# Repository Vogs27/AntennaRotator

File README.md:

# AntennaRotator
This is an improved antenna rotor based on [Satnogs Project rotor V3.1](https://wiki.satnogs.org/SatNOGS_Rotator_v3). It uses the same mechanics but a different custom made controller.

The board uses an ARM based microcontroller (SAMD21) at 48MHz, giving more headroom for future developements. It uses the Arduino Zero core to ease the programming stage. 
TMC2209 are used as drivers to provide a silent experience.

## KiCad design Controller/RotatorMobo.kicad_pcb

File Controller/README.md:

# Controller board

This is the first version of the controller board.
It's a 100mmx100mm 4 layer PCB.

An interactive bom is provided inside ibom folder.
Grbl files are in production folder together with a BOM file. Some LCSC components code are provided for reference.

The board was manufactured at JLCPCB.

## ToDo

Ground trace in TMC2209 is not connected to both ground vias but just to one. After testing this doesn't seems a problem.

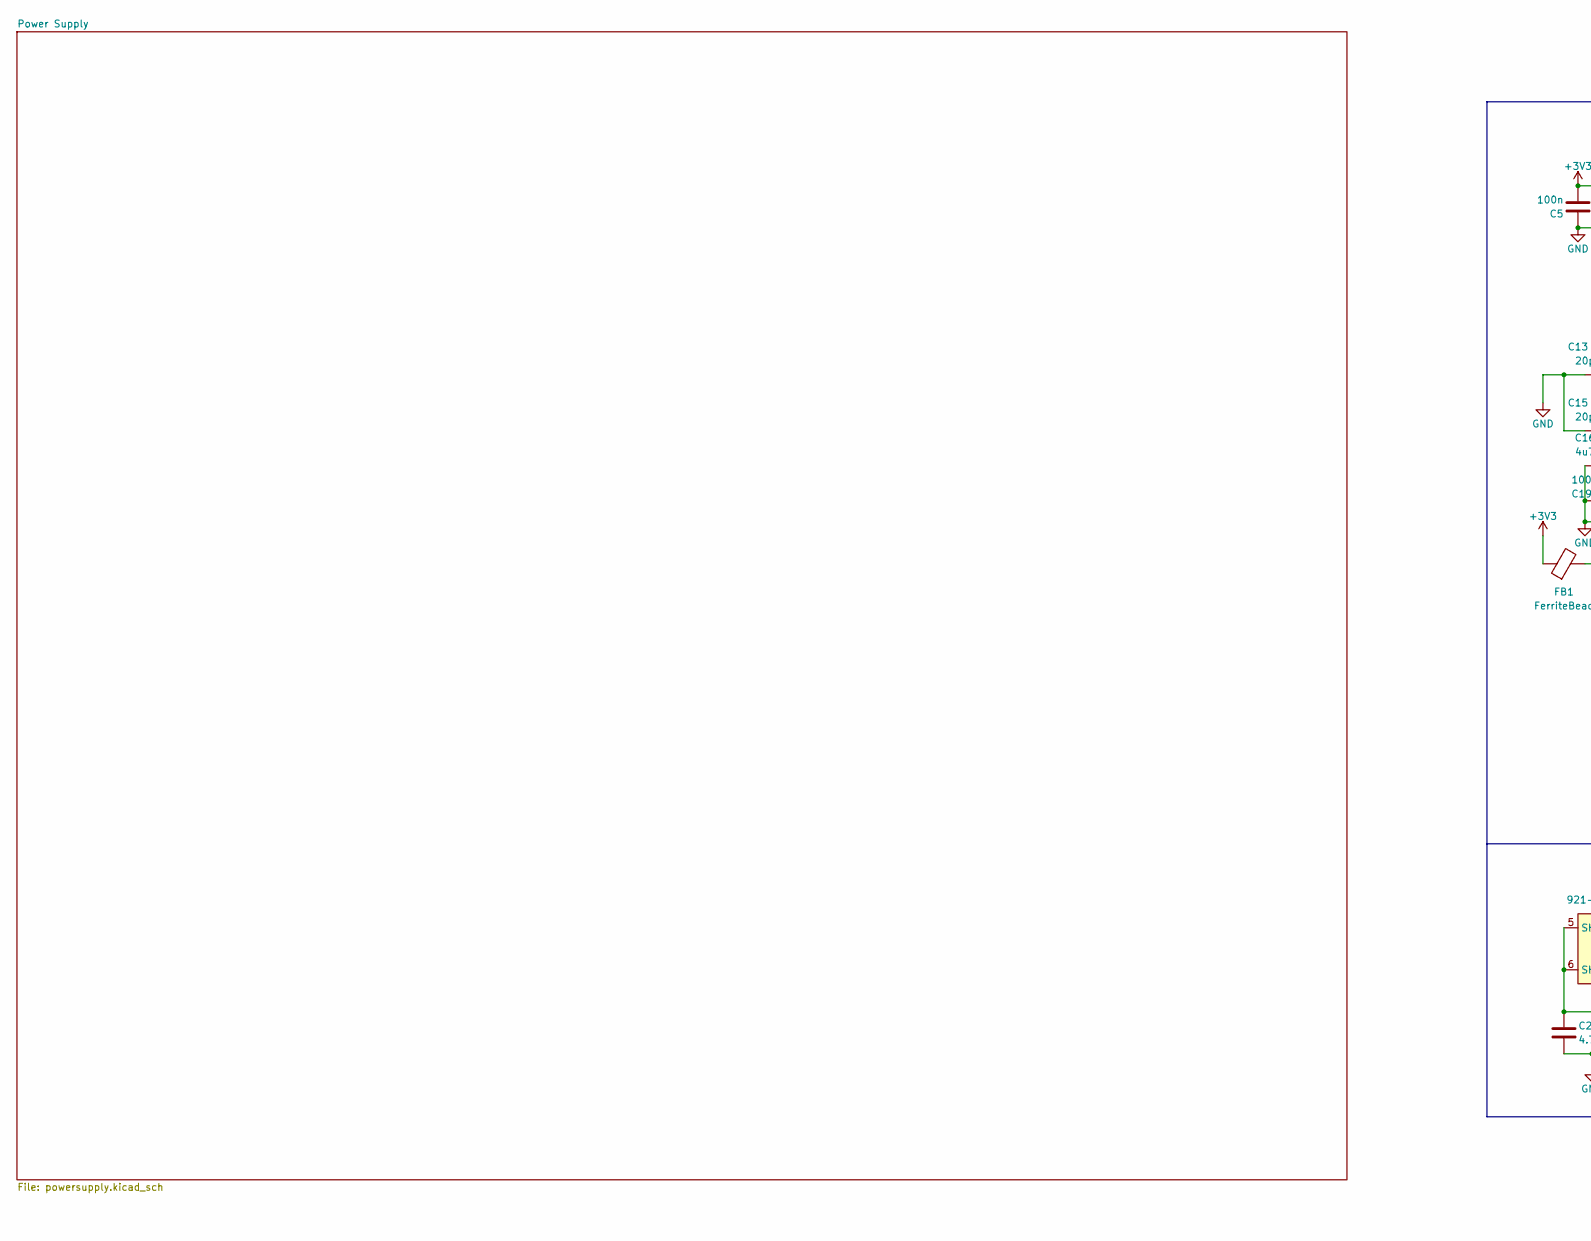
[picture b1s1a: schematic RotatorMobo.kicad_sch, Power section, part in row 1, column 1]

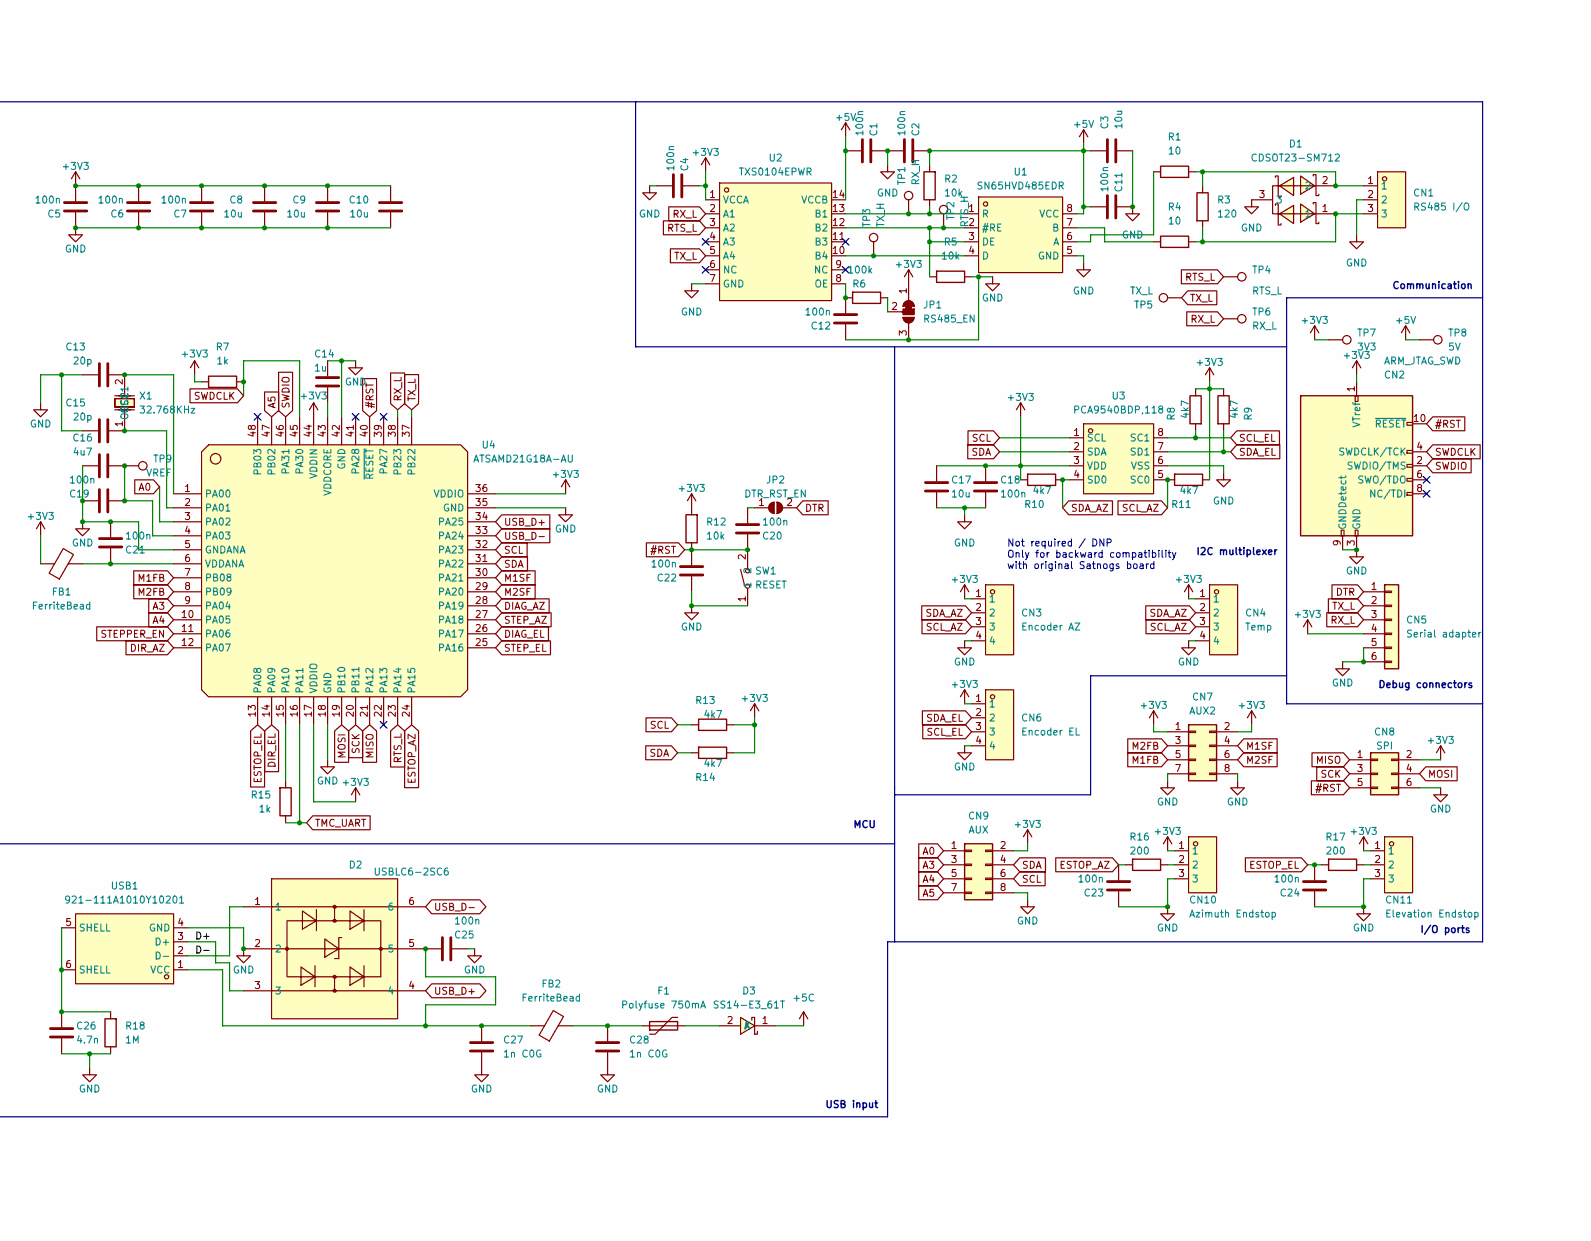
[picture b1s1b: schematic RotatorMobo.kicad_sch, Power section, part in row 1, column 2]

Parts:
C1, C2, C4, C5, C6, C7, C11, C12, C18, C19, C20, C21, C22, C23, C24, C25: 100n; C_0603_1608Metric_Pad1.08x0.95mm_HandSolder; LCSC_id C1591
C3, C8, C9, C10, C17: 10u; R_1206_3216Metric_Pad1.30x1.75mm_HandSolder; LCSC_id C89632
C13, C15: 20p; C_0805_2012Metric_Pad1.18x1.45mm_HandSolder; LCSC_id C1798
C14: 1u; C_0805_2012Metric_Pad1.18x1.45mm_HandSolder; LCSC_id C116352
C16: 4u7; C_0805_2012Metric_Pad1.18x1.45mm_HandSolder; LCSC_id C98192
C26: 4.7n; R_1206_3216Metric_Pad1.30x1.75mm_HandSolder; LCSC_id C571063
C27, C28: 1n C0G; R_0603_1608Metric_Pad0.98x0.95mm_HandSolder; LCSC_id C3909020
CN1: RS485 I/O; PinHeader_1x03_P2.54mm_Vertical; LCSC Part C5341202
CN2: ARM_JTAG_SWD; PinHeader_2x05_P1.27mm_Vertical
CN3: Encoder AZ; PinHeader_1x04_P2.54mm_Vertical; LCSC Part C722867
CN4: Temp; PinHeader_1x04_P2.54mm_Vertical; LCSC Part C722867
CN5: Serial adapter; PinHeader_1x06_P2.54mm_Vertical
CN6: Encoder EL; PinHeader_1x04_P2.54mm_Vertical; LCSC Part C722867
CN7: AUX2; PinHeader_2x04_P2.54mm_Vertical
CN8: SPI; PinHeader_2x03_P2.54mm_Vertical
CN9: AUX; PinHeader_2x04_P2.54mm_Vertical
CN10: Azimuth Endstop; PinHeader_1x03_P2.54mm_Vertical; LCSC Part C5341202
CN11: Elevation Endstop; PinHeader_1x03_P2.54mm_Vertical; LCSC Part C5341202
D1: CDSOT23-SM712; SOT-23_L2.9-W1.3-P1.90-LS2.4-BR; LCSC Part C404012
D2: USBLC6-2SC6; SOT-23-6_L2.9-W1.6-P0.95-LS2.8-BL; LCSC Part C7519
D3: SS14-E3_61T; D_SMA_Handsoldering; LCSC Part C47460
F1: Polyfuse 750mA; Fuse_0805_2012Metric_Pad1.15x1.40mm_HandSolder; LCSC_id C883111
FB1, FB2: FerriteBead; L_0603_1608Metric_Pad1.05x0.95mm_HandSolder; MPN BLM18PG471SN1; LCSC ID C97853
JP1: RS485_EN; SolderJumper-3_P1.3mm_Bridged12_RoundedPad1.0x1.5mm
JP2: DTR_RST_EN; SolderJumper-2_P1.3mm_Open_RoundedPad1.0x1.5mm
R1, R4: 10; R_0603_1608Metric_Pad0.98x0.95mm_HandSolder; LCSC_id C22859
R2, R5, R12: 10k; R_0805_2012Metric_Pad1.20x1.40mm_HandSolder; LCSC_id C25612
R3: 120; R_0603_1608Metric_Pad0.98x0.95mm_HandSolder; LCSC_id C2906988
R6: 100k; R_0805_2012Metric_Pad1.20x1.40mm_HandSolder; LCSC_id C25611
R7, R15: 1k; R_0603_1608Metric_Pad0.98x0.95mm_HandSolder; LCSC_id C21190
R8, R9, R10, R11, R13, R14: 4k7; R_0603_1608Metric_Pad0.98x0.95mm_HandSolder; LCSC_id C25999
R16, R17: 200; R_0603_1608Metric_Pad0.98x0.95mm_HandSolder; LCSC_id C103389
R18: 1M; R_1206_3216Metric_Pad1.30x1.75mm_HandSolder; LCSC_id C175518
SW1: RESET; SW-SMD_L6.1-W3.5-LS8.0; LCSC Part C5117870
TP1: RX_H; TestPoint_Pad_D1.5mm
TP2: RTS_H; TestPoint_Pad_D1.5mm
TP3: TX_H; TestPoint_Pad_D1.5mm
TP4: RTS_L; TestPoint_Pad_D1.5mm
TP5: TX_L; TestPoint_Pad_D1.5mm
TP6: RX_L; TestPoint_Pad_D1.5mm
TP7: 3V3; TestPoint_Pad_D1.5mm
TP8: 5V; TestPoint_Pad_D1.5mm
TP9: VREF; TestPoint_Pad_D1.5mm
U1: SN65HVD485EDR; SOIC-8_L5.0-W4.0-P1.27-LS6.0-BL; LCSC Part C27899
U2: TXS0104EPWR; TSSOP-14_L5.0-W4.4-P0.65-LS6.4-BL; LCSC Part C44955
U3: PCA9540BDP,118; TSSOP-8_L3.0-W3.0-P0.65-LS4.9-BL; LCSC Part C2652901
U4: ATSAMD21G18A-AU; TQFP-48_L7.0-W7.0-P0.50-LS9.0-BL; LCSC Part C78624
USB1: 921-111A1010Y10201; USB-B-TH_921-111A1010Y10201; LCSC Part C2763094
X1: 32.768KHz; OSC-TH_BD1.9-P0.70; LCSC Part C403947

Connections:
#RST: C20.2, C22.1, CN2.10 (~RESET), CN8.5, R12.1, SW1.2, U4.40 (~RESET)
+3V3: C4.2, C5.1, C6.1, C7.1, C8.2, C9.2, C10.2, C17.2, C18.2, CN2.1 (VTref), CN3.1, CN4.1, CN5.4, CN6.1, CN7.1, CN7.2, CN8.2, CN9.2, CN10.1, CN11.1, FB1.1, JP1.1 (A), R7.2, R8.1, R9.1, R10.2, R11.1, R12.2, R13.1, R14.1, TP7.1, U2.1 (VCCA), U3.3 (VDD), U4.17 (VDDIO), U4.36 (VDDIO), U4.44 (VDDIN); also elsewhere on the board
+5C: D3.1 (K); also elsewhere on the board
+5V: C1.1, C2.2, C3.2, C11.1, R2.2, TP8.1, U1.8 (VCC), U2.14 (VCCB); also elsewhere on the board
/D+: D2.3, USB1.3 (D+)
/D-: D2.1, USB1.2 (D-)
A0: CN9.1, U4.3 (PA02)
A3: CN9.3, U4.9 (PA04)
A4: CN9.5, U4.10 (PA05)
A5: CN9.7, U4.47 (PB02)
DIAG_AZ: U4.28 (PA19); also elsewhere on the board
DIAG_EL: U4.26 (PA17); also elsewhere on the board
DIR_AZ: U4.12 (PA07); also elsewhere on the board
DIR_EL: U4.14 (PA09); also elsewhere on the board
DTR: CN5.1, JP2.2 (B)
ESTOP_AZ: C23.1, R16.2, U4.24 (PA15)
ESTOP_EL: C24.1, R17.2, U4.13 (PA08)
GND: C1.2, C2.1, C3.1, C4.1, C5.2, C6.2, C7.2, C8.1, C9.1, C10.1, C11.2, C12.2, C13.1, C14.2, C15.1, C16.1, C17.1, C18.1, C19.1, C21.1, C22.2, C23.2, C24.2, C25.2, C26.1, C27.1, C28.1, CN1.2, CN2.3 (GND), CN2.5 (GND), CN2.9 (GNDDetect), CN3.4, CN4.4, CN5.5, CN5.6, CN6.4, CN7.7, CN7.8, CN8.6, CN9.8, CN10.3, CN11.3, D1.3, D2.2, JP1.3 (B), R5.1, R18.1, SW1.1, U1.5 (GND), U2.7 (GND), U3.6 (VSS), U4.5 (GNDANA), U4.18 (GND), U4.35 (GND), U4.42 (GND), USB1.4 (GND); also elsewhere on the board
M1FB: CN7.5, U4.7 (PB08)
M1SF: CN7.4, U4.30 (PA21)
M2FB: CN7.3, U4.8 (PB09)
M2SF: CN7.6, U4.29 (PA20)
MISO: CN8.1, U4.21 (PA12)
MOSI: CN8.4, U4.19 (PB10)
unnamed: C26.2, R18.2, USB1.5 (SHELL), USB1.6 (SHELL)
unnamed: C28.2, F1.1, FB2.2
unnamed: CN1.1, D1.2, R1.2, R3.1
unnamed: CN1.3, D1.1, R3.2, R4.2
unnamed: CN10.2, R16.1
unnamed: CN11.2, R17.1
unnamed: D3.2 (A), F1.2
unnamed: JP1.2 (C), R6.1
unnamed: C20.1, JP2.1 (A)
unnamed: R5.2, TP2.1, U1.2 (#RE), U1.3 (DE), U2.12 (B2)
unnamed: R1.1, U1.6 (A)
unnamed: R4.1, U1.7 (B)
unnamed: TP3.1, U1.4 (D), U2.10 (B4)
unnamed: R2.1, TP1.1, U1.1 (R), U2.13 (B1)
unnamed: C12.1, R6.2, U2.8 (OE)
unnamed: C13.2, U4.1 (PA00), X1.2 (OSC2)
unnamed: C15.2, U4.2 (PA01), X1.1 (OSC1)
unnamed: C16.2, C19.2, TP9.1, U4.4 (PA03)
unnamed: R15.2, U4.15 (PA10)
unnamed: C21.2, FB1.2, U4.6 (VDDANA)
unnamed: C14.1, U4.43 (VDDCORE)
unnamed: C25.1, C27.2, D2.5, FB2.1, USB1.1 (VCC)
RTS_L: TP4.1, U2.3 (A2), U4.23 (PA14)
RX_L: CN5.3, TP6.1, U2.2 (A1), U4.38 (PB23)
SCK: CN8.3, U4.20 (PB11)
SCL: CN9.6, R13.2, U3.1 (SCL), U4.32 (PA23)
SCL_AZ: CN3.3, CN4.3, R11.2, U3.5 (SC0)
SCL_EL: CN6.3, R8.2, U3.8 (SC1)
SDA: CN9.4, R14.2, U3.2 (SDA), U4.31 (PA22)
SDA_AZ: CN3.2, CN4.2, R10.1, U3.4 (SD0)
SDA_EL: CN6.2, R9.2, U3.7 (SD1)
STEPPER_EN: U4.11 (PA06); also elsewhere on the board
STEP_AZ: U4.27 (PA18); also elsewhere on the board
STEP_EL: U4.25 (PA16); also elsewhere on the board
SWDCLK: CN2.4 (SWDCLK/TCK), R7.1, U4.45 (PA30)
SWDIO: CN2.2 (SWDIO/TMS), U4.46 (PA31)
TMC_UART: R15.1, U4.16 (PA11); also elsewhere on the board
TX_L: CN5.2, TP5.1, U2.5 (A4), U4.37 (PB22)
USB_D+: D2.4, U4.34 (PA25)
USB_D-: D2.6, U4.33 (PA24)

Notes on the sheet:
Communication
I2C multiplexer
Debug connectors
I/O ports
MCU
USB input
Not required / DNP Only for backward compatibility with original Satnogs board

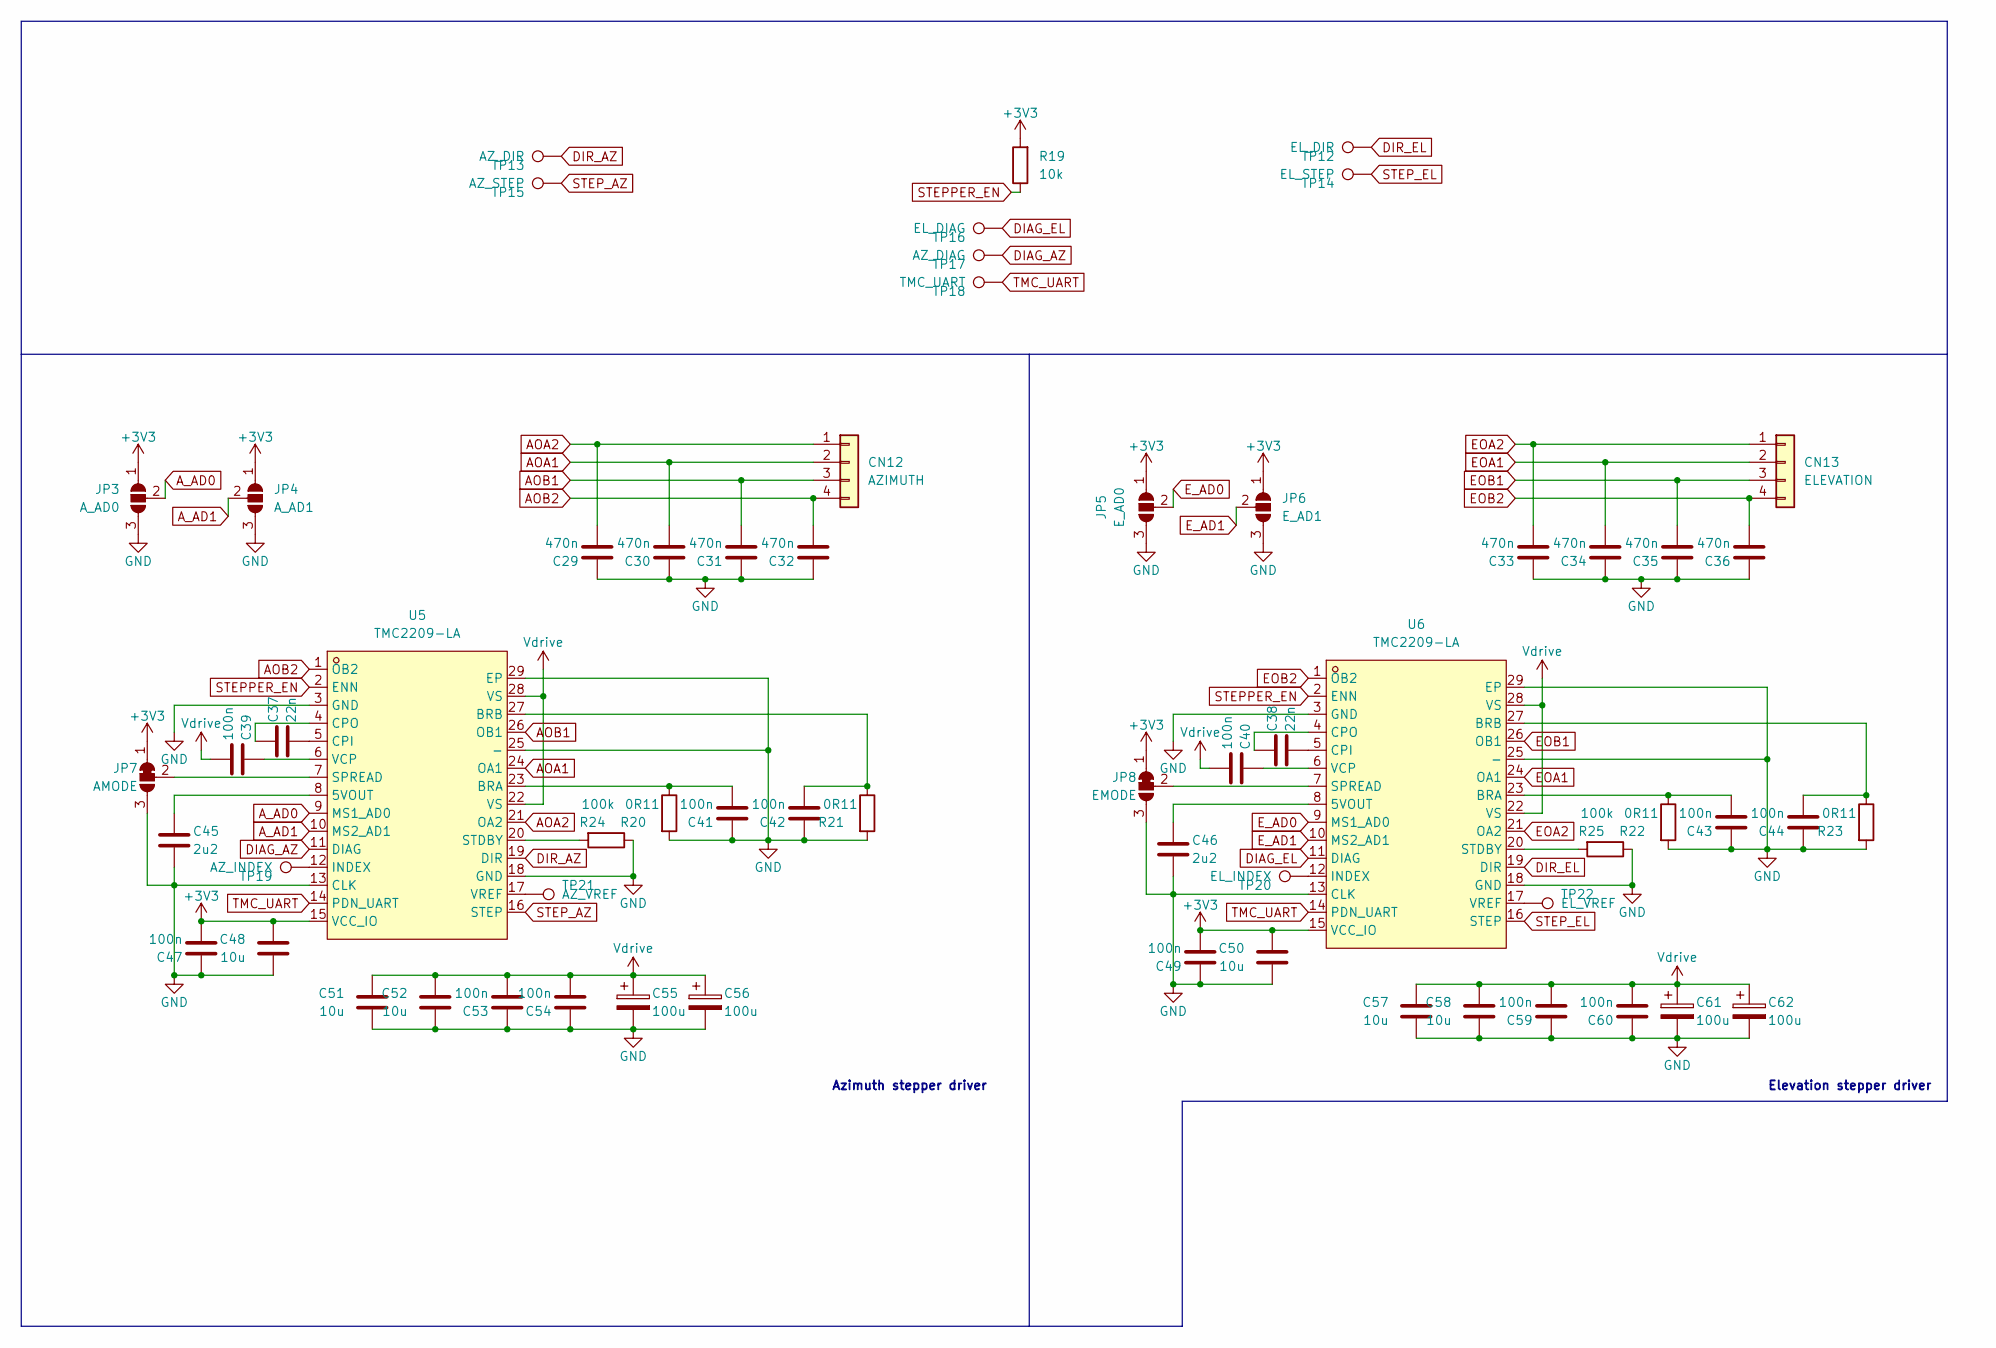
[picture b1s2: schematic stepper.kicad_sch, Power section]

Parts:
C29, C30, C31, C32, C33, C34, C35, C36: 470n; C_1812_4532Metric_Pad1.57x3.40mm_HandSolder; LCSC_id C152994
C37, C38: 22n; C_0603_1608Metric_Pad1.08x0.95mm_HandSolder; LCSC_id C21122
C39, C40, C41, C42, C43, C44, C47, C49, C53, C54, C59, C60: 100n; C_0603_1608Metric_Pad1.08x0.95mm_HandSolder; LCSC_id C1591
C45, C46: 2u2; C_0603_1608Metric_Pad1.08x0.95mm_HandSolder; LCSC_id C23630
C48, C50, C51, C52, C57, C58: 10u; R_1206_3216Metric_Pad1.30x1.75mm_HandSolder; LCSC_id C89632
C55, C56, C61, C62: 100u; CP_Radial_D8.0mm_P3.50mm
CN12: AZIMUTH; PinHeader_1x04_P2.54mm_Vertical
CN13: ELEVATION; PinHeader_1x04_P2.54mm_Vertical
JP3: A_AD0; SolderJumper-3_P1.3mm_Open_RoundedPad1.0x1.5mm
JP4: A_AD1; SolderJumper-3_P1.3mm_Open_RoundedPad1.0x1.5mm
JP5: E_AD0; SolderJumper-3_P1.3mm_Open_RoundedPad1.0x1.5mm
JP6: E_AD1; SolderJumper-3_P1.3mm_Open_RoundedPad1.0x1.5mm
JP7: AMODE; SolderJumper-3_P1.3mm_Bridged12_RoundedPad1.0x1.5mm
JP8: EMODE; SolderJumper-3_P1.3mm_Bridged12_RoundedPad1.0x1.5mm
R19: 10k; R_0805_2012Metric_Pad1.20x1.40mm_HandSolder; LCSC_id C25612
R20, R21, R22, R23: 0R11; R_2512_6332Metric_Pad1.40x3.35mm_HandSolder; LCSC_id C333708
R24, R25: 100k; R_0805_2012Metric_Pad1.20x1.40mm_HandSolder; LCSC_id C25611
TP12: EL_DIR; TestPoint_Pad_D1.5mm
TP13: AZ_DIR; TestPoint_Pad_D1.5mm
TP14: EL_STEP; TestPoint_Pad_D1.5mm
TP15: AZ_STEP; TestPoint_Pad_D1.5mm
TP16: EL_DIAG; TestPoint_Pad_D1.5mm
TP17: AZ_DIAG; TestPoint_Pad_D1.5mm
TP18: TMC_UART; TestPoint_Pad_D1.5mm
TP19: AZ_INDEX; TestPoint_Pad_D1.5mm
TP20: EL_INDEX; TestPoint_Pad_D1.5mm
TP21: AZ_VREF; TestPoint_Pad_D1.5mm
TP22: EL_VREF; TestPoint_Pad_D1.5mm
U5, U6: TMC2209-LA; QFN-28_L5.0-W5.0-P0.50-BL-EP; LCSC Part C465949

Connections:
+3V3: C47.1, C48.2, C49.1, C50.2, JP3.1 (A), JP4.1 (A), JP5.1 (A), JP6.1 (A), JP7.1 (A), JP8.1 (A), R19.2, U5.15 (VCC_IO), U6.15 (VCC_IO); also elsewhere on the board
AOA1: C30.1, CN12.2, U5.24 (OA1)
AOA2: C29.1, CN12.1, U5.21 (OA2)
AOB1: C31.1, CN12.3, U5.26 (OB1)
AOB2: C32.1, CN12.4, U5.1 (OB2)
A_AD0: JP3.2 (C), U5.9 (MS1_AD0)
A_AD1: JP4.2 (C), U5.10 (MS2_AD1)
DIAG_AZ: TP17.1, U5.11 (DIAG); also elsewhere on the board
DIAG_EL: TP16.1, U6.11 (DIAG); also elsewhere on the board
DIR_AZ: TP13.1, U5.19 (DIR); also elsewhere on the board
DIR_EL: TP12.1, U6.19 (DIR); also elsewhere on the board
EOA1: C34.1, CN13.2, U6.24 (OA1)
EOA2: C33.1, CN13.1, U6.21 (OA2)
EOB1: C35.1, CN13.3, U6.26 (OB1)
EOB2: C36.1, CN13.4, U6.1 (OB2)
E_AD0: JP5.2 (C), U6.9 (MS1_AD0)
E_AD1: JP6.2 (C), U6.10 (MS2_AD1)
GND: C29.2, C30.2, C31.2, C32.2, C33.2, C34.2, C35.2, C36.2, C41.2, C42.2, C43.2, C44.2, C45.1, C46.1, C47.2, C48.1, C49.2, C50.1, C51.1, C52.1, C53.2, C54.2, C55.2, C56.2, C57.1, C58.1, C59.2, C60.2, C61.2, C62.2, JP3.3 (B), JP4.3 (B), JP5.3 (B), JP6.3 (B), JP7.3 (B), JP8.3 (B), R20.2, R21.2, R22.2, R23.2, R24.1, R25.1, U5.3 (GND), U5.13 (CLK), U5.18 (GND), U5.25 (-), U5.29 (EP), U6.3 (GND), U6.13 (CLK), U6.18 (GND), U6.25 (-), U6.29 (EP); also elsewhere on the board
unnamed: JP7.2 (C), U5.7 (SPREAD)
unnamed: JP8.2 (C), U6.7 (SPREAD)
unnamed: C45.2, U5.8 (5VOUT)
unnamed: C41.1, R20.1, U5.23 (BRA)
unnamed: C42.1, R21.1, U5.27 (BRB)
unnamed: C37.1, U5.5 (CPI)
unnamed: C37.2, U5.4 (CPO)
unnamed: TP19.1, U5.12 (INDEX)
unnamed: R24.2, U5.20 (STDBY)
unnamed: C39.2, U5.6 (VCP)
unnamed: TP21.1, U5.17 (VREF)
unnamed: C46.2, U6.8 (5VOUT)
unnamed: C43.1, R22.1, U6.23 (BRA)
unnamed: C44.1, R23.1, U6.27 (BRB)
unnamed: C38.1, U6.5 (CPI)
unnamed: C38.2, U6.4 (CPO)
unnamed: TP20.1, U6.12 (INDEX)
unnamed: R25.2, U6.20 (STDBY)
unnamed: C40.2, U6.6 (VCP)
unnamed: TP22.1, U6.17 (VREF)
STEPPER_EN: R19.1, U5.2 (ENN), U6.2 (ENN); also elsewhere on the board
STEP_AZ: TP15.1, U5.16 (STEP); also elsewhere on the board
STEP_EL: TP14.1, U6.16 (STEP); also elsewhere on the board
TMC_UART: TP18.1, U5.14 (PDN_UART), U6.14 (PDN_UART); also elsewhere on the board
Vdrive: C39.1, C40.1, C51.2, C52.2, C53.1, C54.1, C55.1, C56.1, C57.2, C58.2, C59.1, C60.1, C61.1, C62.1, U5.22 (VS), U5.28 (VS), U6.22 (VS), U6.28 (VS); also elsewhere on the board

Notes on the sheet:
Azimuth stepper driver
Elevation stepper driver

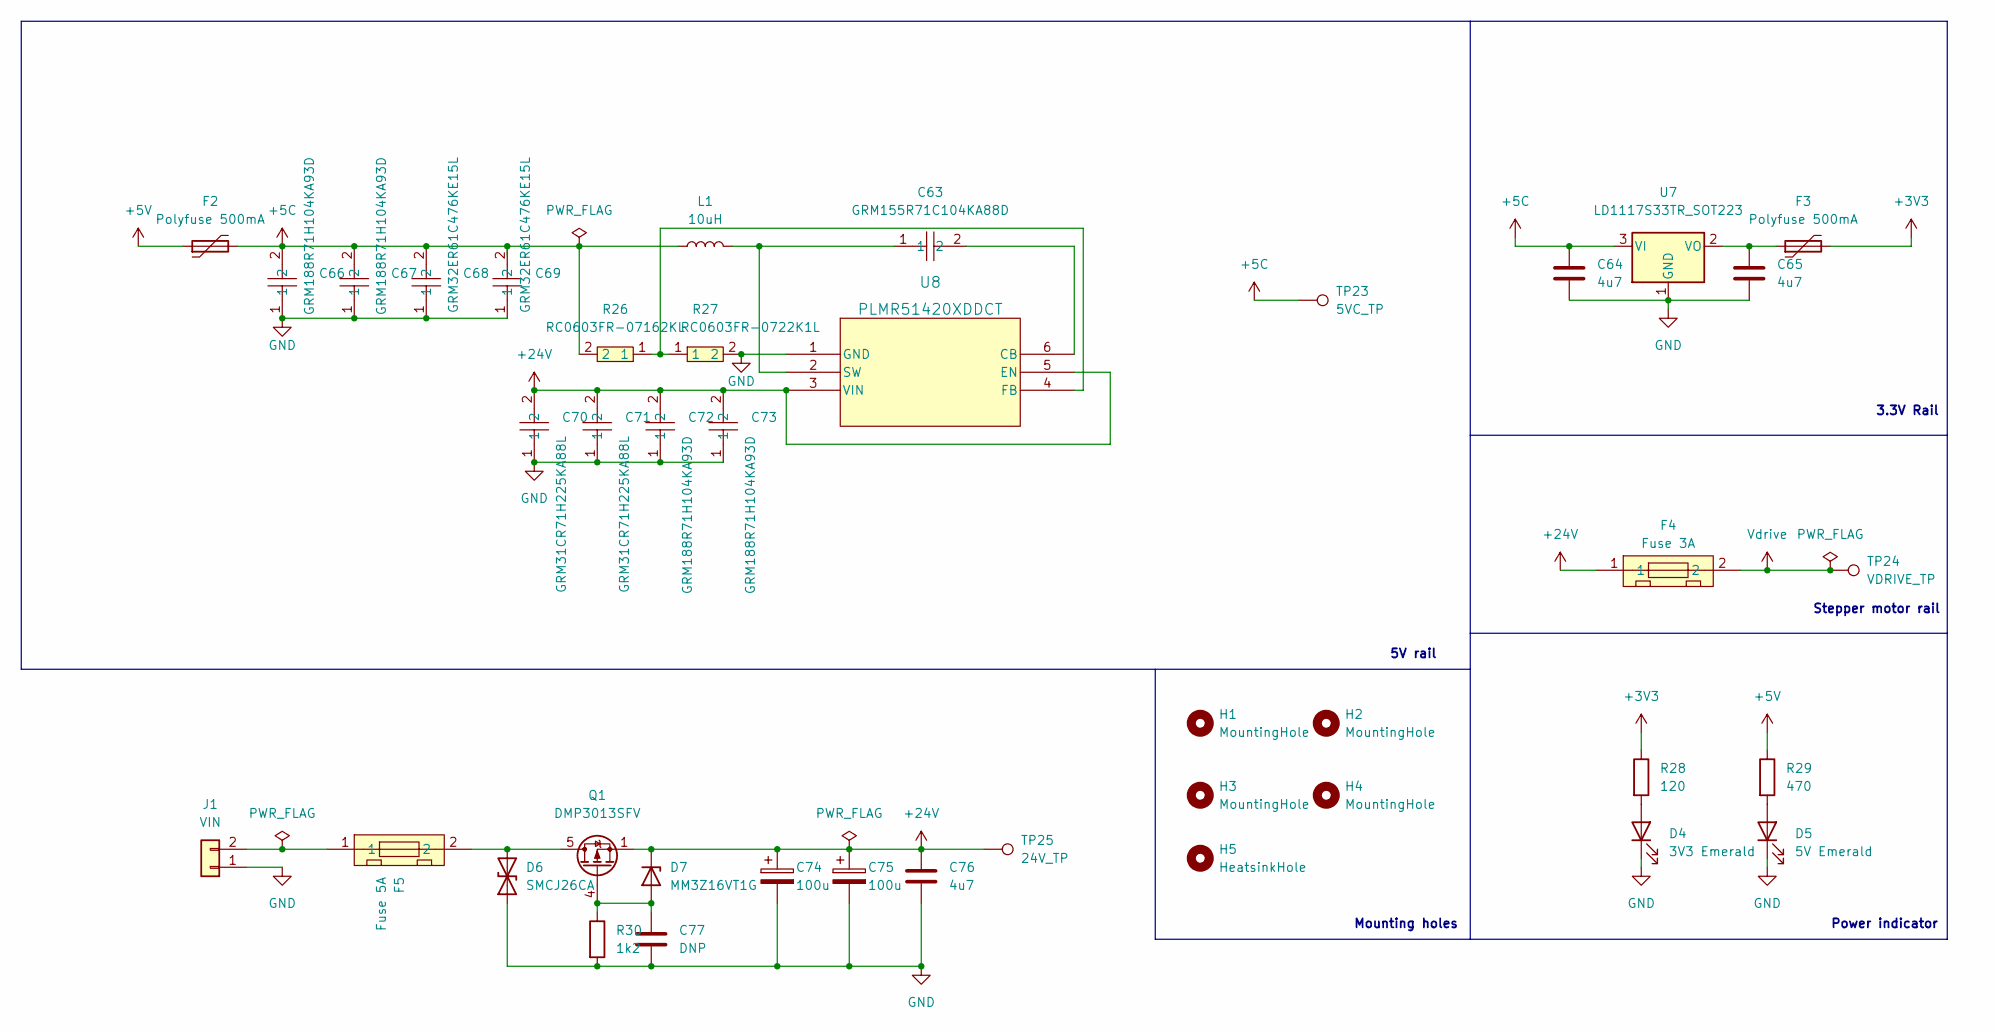
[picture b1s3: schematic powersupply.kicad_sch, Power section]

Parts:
C63: GRM155R71C104KA88D; C0402; LCSC Part C71629
C64, C65, C76: 4u7; C_0805_2012Metric_Pad1.18x1.45mm_HandSolder; LCSC_id C98192
C66, C67, C72, C73: GRM188R71H104KA93D; C0603; LCSC Part C77055
C68, C69: GRM32ER61C476KE15L; C1210; LCSC Part C77101
C70, C71: GRM31CR71H225KA88L; C1206; LCSC Part C77095
C74, C75: 100u; CP_Radial_D8.0mm_P3.50mm
C77: DNP; C_0805_2012Metric_Pad1.18x1.45mm_HandSolder
D4: 3V3 Emerald; LED_0805_2012Metric_Pad1.15x1.40mm_HandSolder; LCSC_id C965815
D5: 5V Emerald; LED_0805_2012Metric_Pad1.15x1.40mm_HandSolder; LCSC_id C965815
D6: SMCJ26CA; D_SMC_Handsoldering; LCSC_id C151280
D7: MM3Z16VT1G; D_SOD-323_HandSoldering; LCSC_id C150089
F2, F3: Polyfuse 500mA; Fuse_1812_4532Metric_Pad1.30x3.40mm_HandSolder; LCSC_id C2649901
F4: Fuse 3A; FUSE-TH_XF-506P; LCSC_id C2935468
F5: Fuse 5A; FUSE-TH_XF-506P; LCSC_id C2935468
H1, H2, H3, H4: MountingHole; MountingHole_3.2mm_M3
H5: HeatsinkHole; MountingHole_3.2mm_M3
J1: VIN; JST_VH_B2P-VH-B_1x02_P3.96mm_Vertical
L1: 10uH; L_Bourns_SRR1260; LCSC_id C2041557
Q1: DMP3013SFV; Diodes_PowerDI3333-8; LCSC_id C264098
R26: RC0603FR-07162KL; R0603; LCSC Part C165760
R27: RC0603FR-0722K1L; R0603; LCSC Part C137768
R28: 120; R_0603_1608Metric_Pad0.98x0.95mm_HandSolder; LCSC_id C2906988
R29: 470; R_0603_1608Metric_Pad0.98x0.95mm_HandSolder; LCSC_id C5140094
R30: 1k2; R_0603_1608Metric_Pad0.98x0.95mm_HandSolder; LCSC_id C25987
TP23: 5VC_TP; TestPoint_Pad_D1.5mm
TP24: VDRIVE_TP; TestPoint_Pad_D1.5mm
TP25: 24V_TP; TestPoint_Pad_D1.5mm
U7: LD1117S33TR_SOT223; SOT-223-3_TabPin2; LCSC_id C35879
U8: PLMR51420XDDCT; SOT-23-THIN-6_DDC_TEX; LCSC_id C5246146

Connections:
+3V3: F3.2, R28.1; also elsewhere on the board
+5C: C64.1, C66.2, C67.2, C68.2, C69.2, F2.2, L1.1, R26.2, TP23.1, U7.3 (VI); also elsewhere on the board
+5V: F2.1, R29.1; also elsewhere on the board
+24V: C70.2, C71.2, C72.2, C73.2, C74.1, C75.1, C76.1, D7.1 (K), F4.1, Q1.1 (S), Q1.2 (S), Q1.3 (S), TP25.1, U8.3 (VIN), U8.5 (EN)
GND: C64.2, C65.2, C66.1, C67.1, C68.1, C69.1, C70.1, C71.1, C72.1, C73.1, C74.2, C75.2, C76.2, C77.2, D4.1 (K), D5.1 (K), D6.1 (A1), J1.1, R27.2, R30.2, U7.1 (GND), U8.1 (GND); also elsewhere on the board
unnamed: D4.2 (A), R28.2
unnamed: D5.2 (A), R29.2
unnamed: D6.2 (A2), F5.2, Q1.5 (D)
unnamed: C77.1, D7.2 (A), Q1.4 (G), R30.1
unnamed: F5.1, J1.2
unnamed: C65.1, F3.1, U7.2 (VO)
unnamed: C63.2, U8.6 (CB)
unnamed: R26.1, R27.1, U8.4 (FB)
unnamed: C63.1, L1.2, U8.2 (SW)
Vdrive: F4.2, TP24.1; also elsewhere on the board

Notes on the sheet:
Stepper motor rail
5V rail
Mounting holes
3.3V Rail
Power indicator

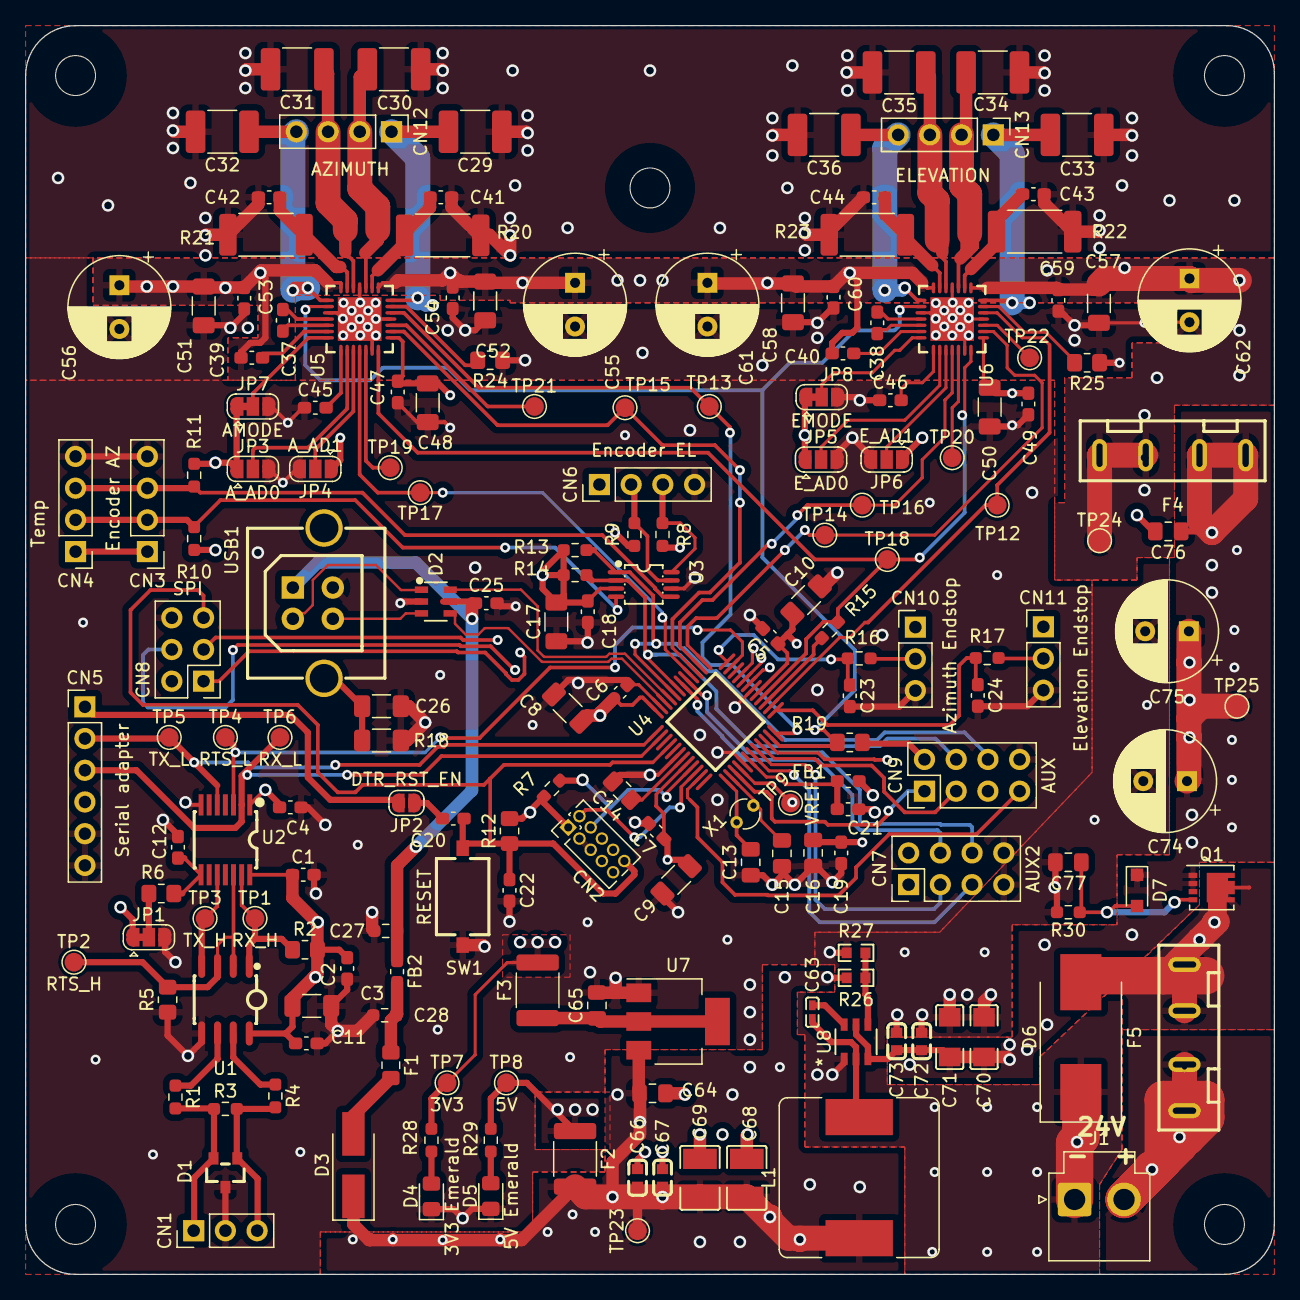
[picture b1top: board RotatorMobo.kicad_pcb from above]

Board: 4 copper layers, 100.0 x 100.0 mm, 184 parts (0 on the bottom side), 107 nets.

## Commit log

2024-02-20 Create LICENSE
